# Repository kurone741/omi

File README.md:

# omi

Omi is a simple desktop companion. Functionality includes date/time, timer, stopwatch, countdown, and audio visualizer which responds to the sounds in your working space (e.g. typing). It can also display humidity and temperature of your working space. It's a device that is for the most part single-purpose, meaning it doesn't occupy more of your attention than it needs.

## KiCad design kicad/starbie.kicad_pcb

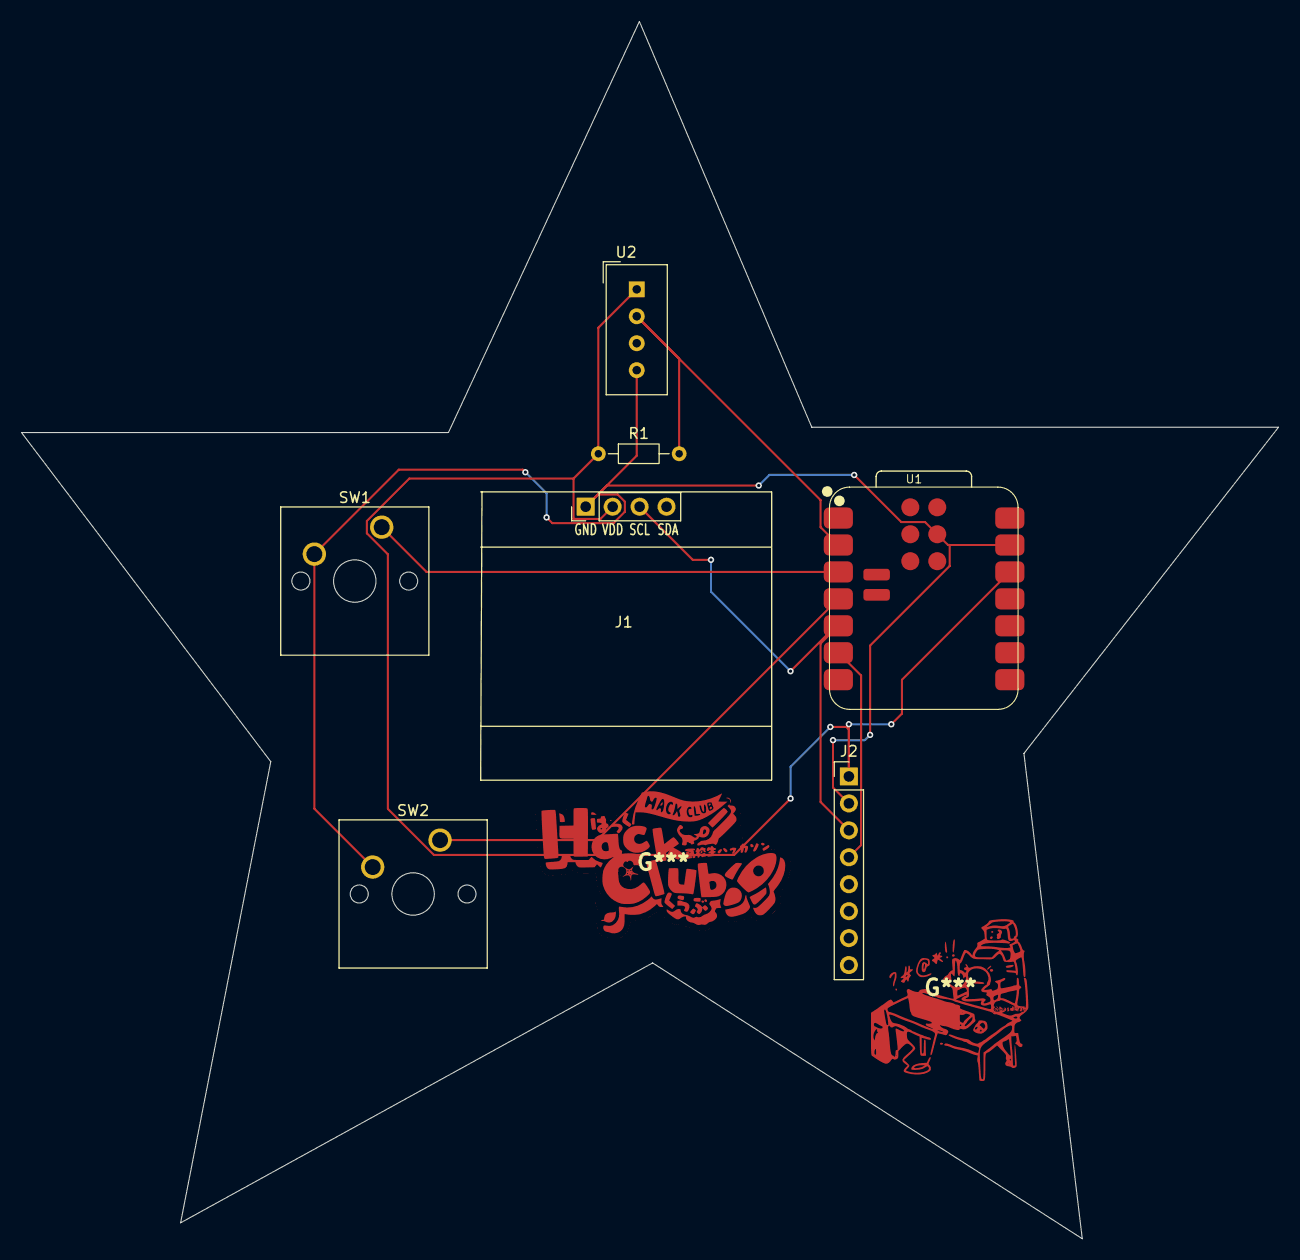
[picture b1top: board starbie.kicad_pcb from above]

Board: 2 copper layers, 118.5 x 114.8 mm, 7 parts (0 on the bottom side), 7 nets.

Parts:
J1: Conn_01x04_Pin; Display_128x64_096_I2C
J2: Conn_01x08_Pin; PinHeader_1x08_P2.54mm_Vertical
R1: 10k; R_Axial_DIN0204_L3.6mm_D1.6mm_P7.62mm_Horizontal
SW1, SW2: SW_Push; SW_Cherry_MX_1.00u_PCB
U1: XIAO-ESP32-C3-SMD
U2: DHT11; Aosong_DHT11_5.5x12.0_P2.54mm

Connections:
+3.3V: J1.2, J2.1, R1.1, U1.12 (3V3_OUT), U2.1 (VDD)
/DHT11 DATA: R1.2, U1.2 (D1), U2.2 (DATA)
/GPIO2: SW1.1, U1.3 (D2)
/GPIO3: SW2.1, U1.4 (D3)
/SCL: J1.3, J2.3, U1.5 (D4)
/SDA: J2.4, U1.6 (D5)
GND: J1.1, J2.2, SW1.2, SW2.2, U1.13 (GND), U1.18 (GND), U2.4 (GND)
